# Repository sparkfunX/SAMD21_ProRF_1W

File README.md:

SparkFun SAMD21 Pro RF 1W 
========================================

[*SparkFun SAMD21 Pro RF 1W  (SPX-14984)*](https://www.sparkfun.com/products/14984)

LoRa stands for 'Long-Range,' referring to a modulation technique whose specialty is low power transmission of small data packets -- perfect for Internet of Things applications. Using either point-to-point radio or LoRaWAN you can send data from a node in a remote location back to your base station to check in on sensors or track equipment. Communication is possible in the other direction as well to send commands or control actuators!

Like the [LoRa®-enabled SparkX Pro RF](https://www.sparkfun.com/products/14785) this board is based on the Semtech SX1276 transceiver, but the module boasts a whopping 1W output power. All that extra oomph makes it possible to send small messages up to 9 miles using common rubber-duck type antennas. 

In addition to more transmission power the SparkX SAMD21 ProRF 1W gets more computational power courtesy of the SAMD21 microcontroller running at 48 MHz. We used the additional GPIO pins to permanently enable LoRaWAN signals. This means more pins for you to connect to sensors and actuators, even when connecting to a LoRaWAN network like [The Things Network](https://console.thethingsnetwork.org/). 

SparkFun labored with love to create this code. Feel like supporting open source hardware? 
Buy a [board](https://www.sparkfun.com/products/14984) from SparkFun!

Repository Contents
-------------------

* **/Documents** - Datasheets
* **/Hardware** - Eagle design files (.brd, .sch)

License Information
-------------------

This product is _**open source**_! 

If you have any questions or concerns on licensing, please contact techsupport@sparkfun.com.

Please use, reuse, and modify these files as you see fit. Please maintain attribution to SparkFun Electronics and release any derivative under the same license.

Distributed as-is; no warranty is given.

- Your friends at SparkFun.

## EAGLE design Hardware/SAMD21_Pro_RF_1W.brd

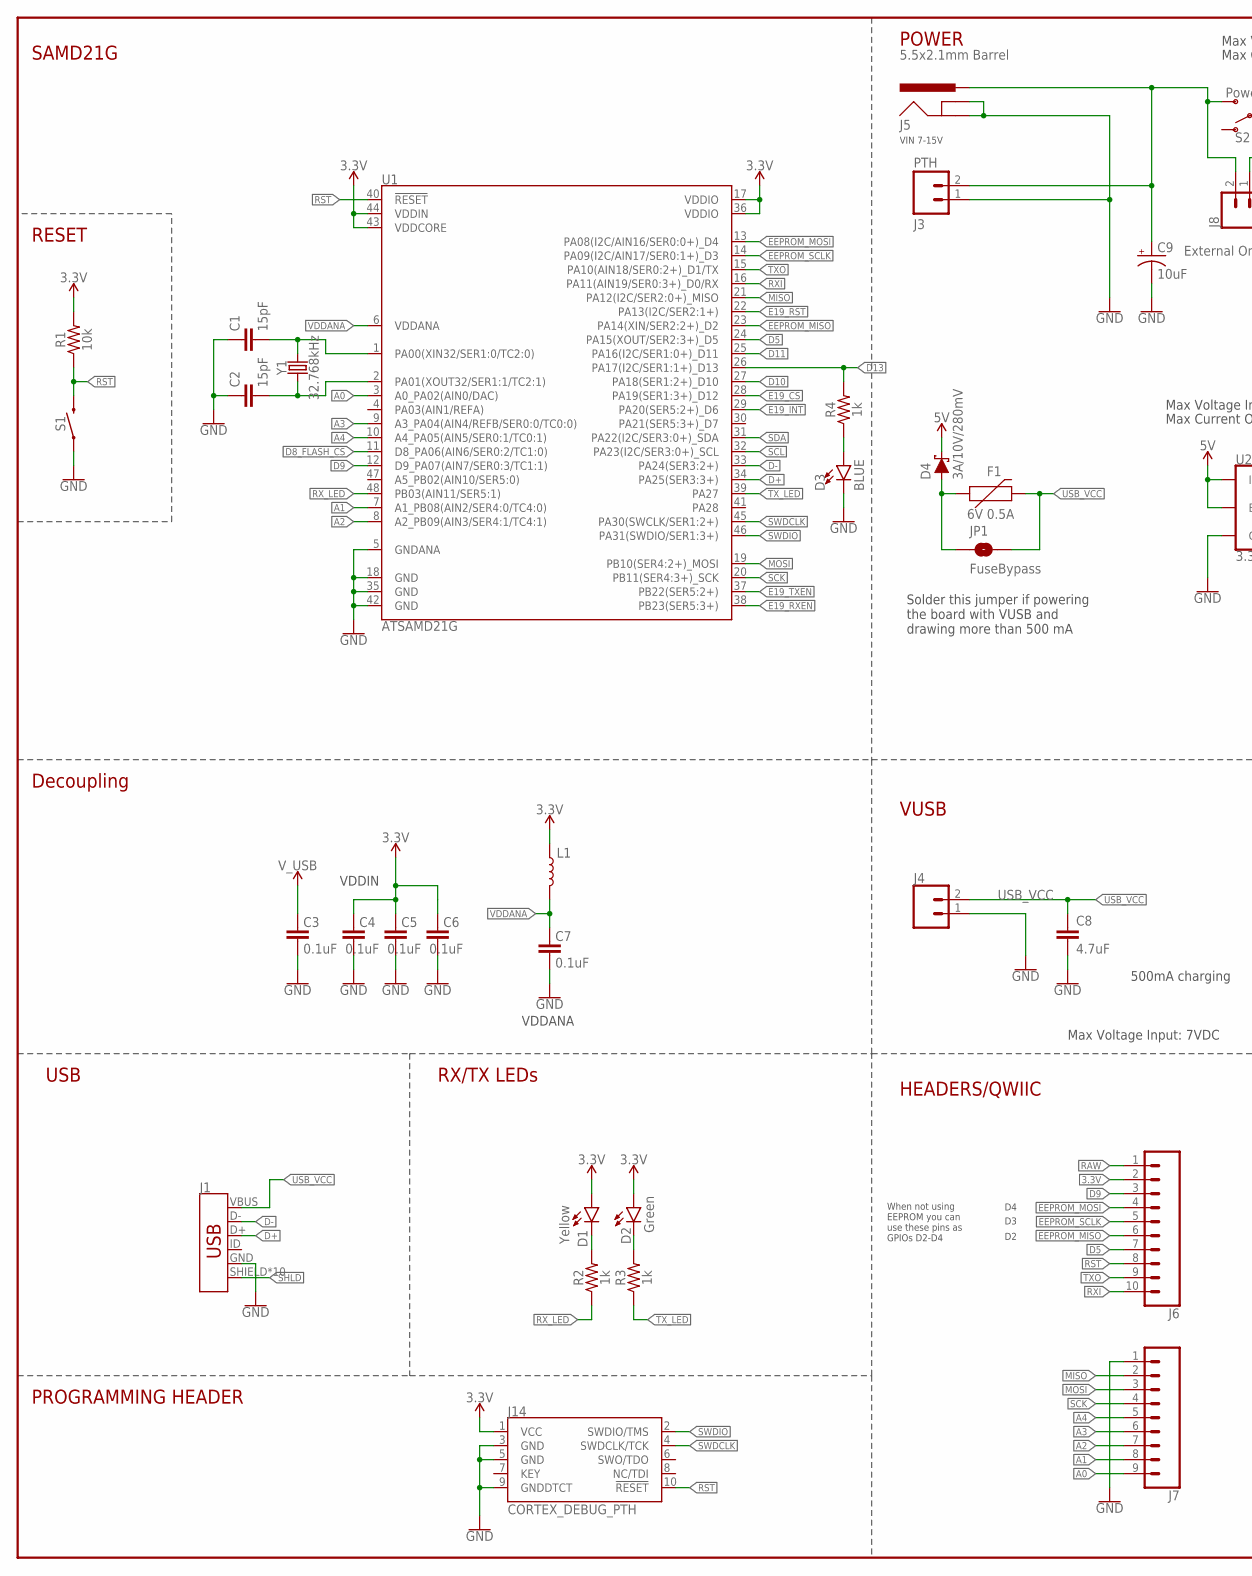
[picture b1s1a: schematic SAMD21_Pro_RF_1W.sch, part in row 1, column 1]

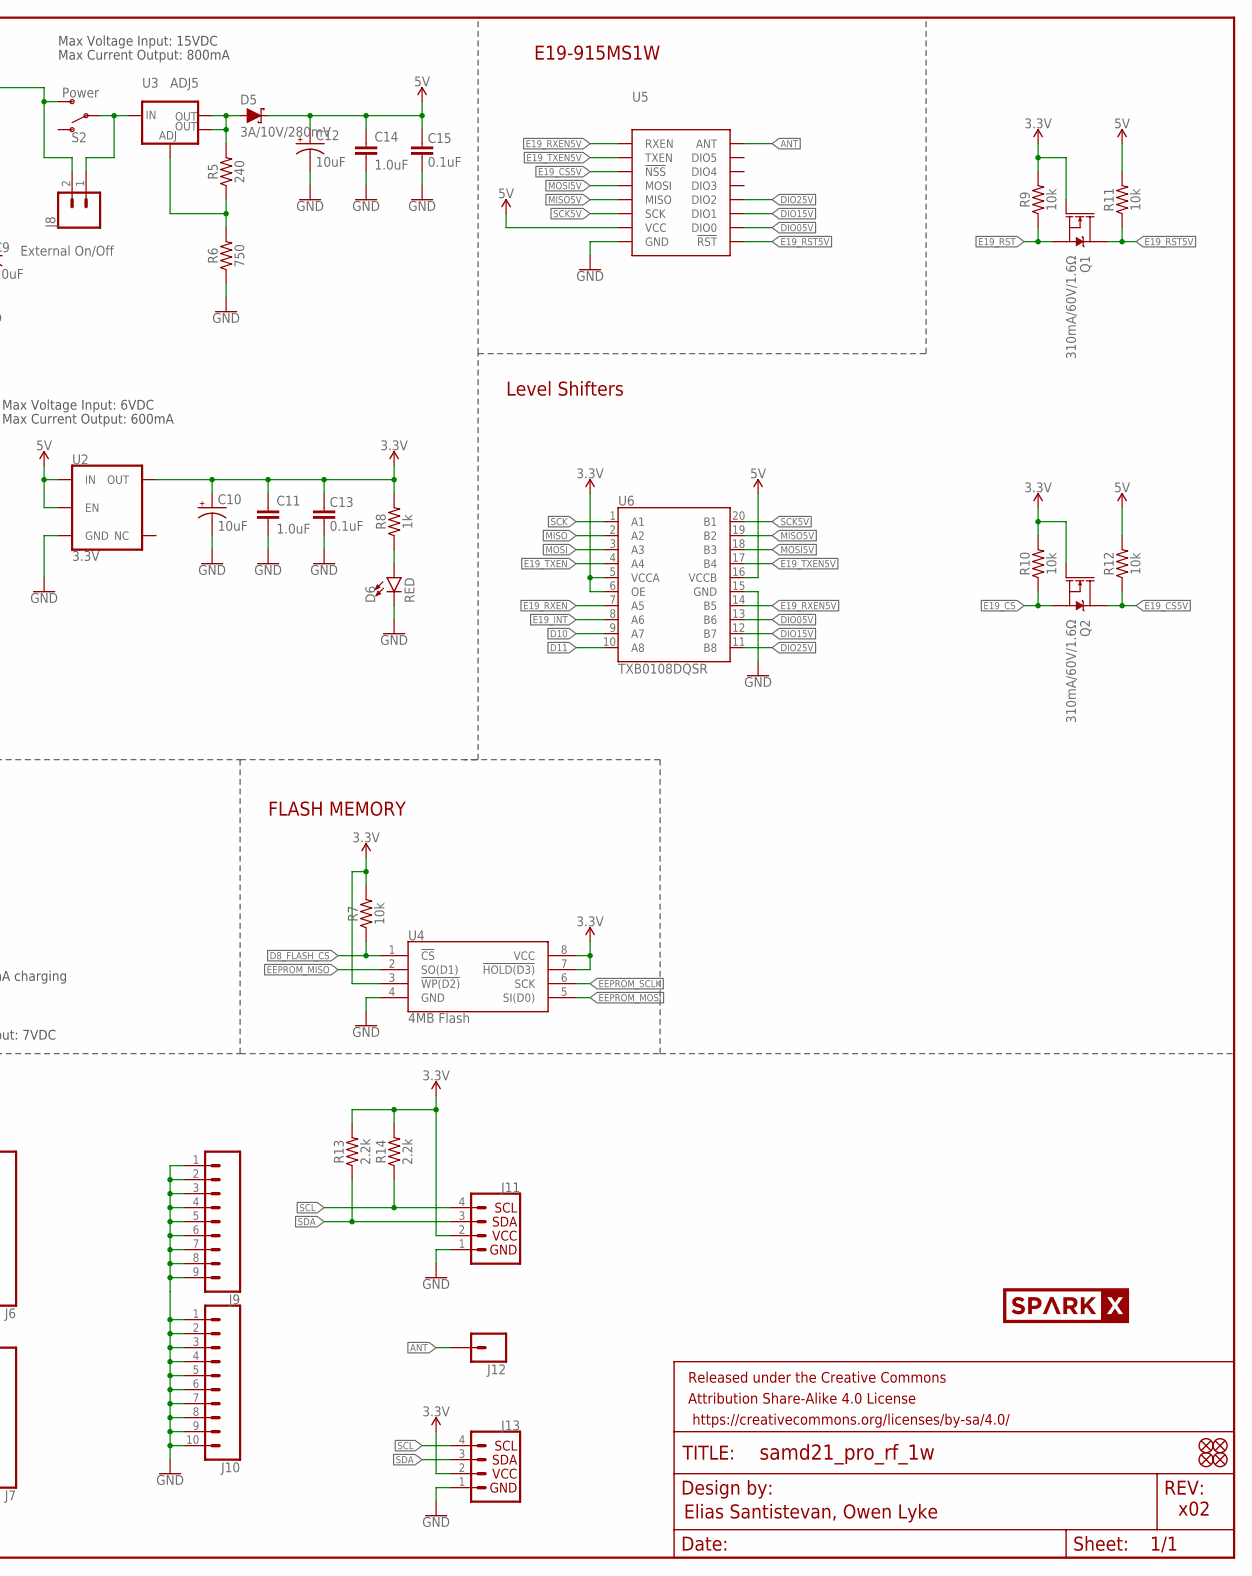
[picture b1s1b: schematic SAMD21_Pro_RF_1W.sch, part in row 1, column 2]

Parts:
C1, C2: 15pF; 0603
C3, C4, C5, C6, C7, C13, C15: 0.1uF; 0603
C8: 4.7uF; 0603
C9, C10, C12: 10uF; EIA3216
C11, C14: 1.0uF; 0603
D1: Yellow; LED-0603
D2: Green; LED-0603
D3: BLUE; LED-0603
D4, D5: 3A/10V/280mV; SOD-323
D6: RED; LED-0603
F1: 6V 0.5A; 0805
FD1, FD2, FD3, FD4: FIDUCIAL1X2; FIDUCIAL-1X2
FRAME1: FRAME-LEDGER; CREATIVE_COMMONS
J1: USB_MICRO-B_HALF_PTH_MILL; USB-MICROB-PTH-MILL
J3: PTH; 1X02_NO_SILK
J4: CONN_021X02_NO_SILK; 1X02_NO_SILK
J5: 5.5x2.1mm Barrel; POWER_JACK_SMD
J6, J10: CONN_10NO_SILK_PTH_FEMALE; 1X10_NO_SILK
J7, J9: CONN_09NO_SILK; 1X09_NO_SILK
J8: External On/Off; 1X02_NO_SILK
J11, J13: QWIIC_CONNECTORJS-1MM; 1X04_1MM_RA
J12: CONN_01PTH_NO_SILK_YES_STOP; 1X01_NO_SILK
J14: CORTEX_DEBUG_PTH; 2X5-PTH-1.27MM
JP1: FuseBypass; SMT-JUMPER_2_NO_SILK
L1: INDUCTORFB-30OHM; 0603
Q1, Q2: 310mA/60V/1.6Ω; SOT323
R1, R7, R9, R10, R11, R12: 10k; 0603
R2, R3, R4, R8: 1k; 0603
R5: 240; 0603
R6: 750; 0603
R13, R14: 2.2k; 0603
S1: MOMENTARY-SWITCH-SPST-SMD-5.2-REDUNDANT; TACTILE_SWITCH_SMD_5.2MM
S2: Power; SWITCH_SPST_SMD_A
U1: ATSAMD21G; QFN-48_NO_EXPOSED_PAD
U2: 3.3V; SOT23-5
U3: ADJ5; SOT223
U4: 4MB Flash; SO08
U5: E19-915MS1W
U6: TXB0108DQSR; UFDFN-20
U$34: SPARKX-LOGO4; SPARKX-MEDIUM
Y1: 32.768kHz; CRYSTAL-SMD-3.2X1.5MM

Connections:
3.3V: C4.2, C5.2, C6.2, C10.+, C11.1, C13.2, D1.A, D2.A, J6.2, J11.2, J13.2, J14.1 (VCC), L1.1, Q1.1 (G), Q2.1 (G), R1.2, R7.2, R8.2, R9.2, R10.2, R13.2, R14.2, U1.17 (VDDIO), U1.36 (VDDIO), U1.43 (VDDCORE), U1.44 (VDDIN), U2.5 (OUT), U4.3 (!WP(D2)), U4.7 (!HOLD(D3)), U4.8 (VCC), U6.5 (VCCA), U6.6 (OE)
5V: C12.+, C14.1, C15.2, D4.C, D5.C, R11.2, R12.2, U2.1 (IN), U2.3 (EN), U5.P$11 (VCC), U6.16 (VCCB)
!E19_CS: Q2.2 (S), R10.1, U1.28 (PA19(SER1:3+)_D12)
!E19_CS5V: Q2.3 (D), R12.1, U5.P$15 (!NSS)
!E19_RST: Q1.2 (S), R9.1, U1.22 (PA13(I2C/SER2:1+))
!E19_RST5V: Q1.3 (D), R11.1, U5.P$8 (!RST)
!RST: J6.8, J14.10 (!RESET), R1.1, S1.3 (2), S1.4 (2), U1.40 (!RESET!)
A0: J7.9, U1.3 (A0_PA02(AIN0/DAC))
A1: J7.8, U1.7 (A1_PB08(AIN2/SER4:0/TC4:0))
A2: J7.7, U1.8 (A2_PB09(AIN3/SER4:1/TC4:1))
A3: J7.6, U1.9 (A3_PA04(AIN4/REFB/SER0:0/TC0:0))
A4: J7.5, U1.10 (A4_PA05(AIN5/SER0:1/TC0:1))
ANT: J12.1, U5.P$19 (ANT)
D5: J6.7, U1.24 (PA15(XOUT/SER2:3+)_D5)
D8_!FLASH_CS: R7.1, U1.11 (D8_PA06(AIN6/SER0:2/TC1:0)), U4.1 (!CS)
D9: J6.3, U1.12 (D9_PA07(AIN7/SER0:3/TC1:1))
D10: U1.27 (PA18(SER1:2+)_D10), U6.9 (A7)
D11: U1.25 (PA16(I2C/SER1:0+)_D11), U6.10 (A8)
D13: R4.2, U1.26 (PA17(I2C/SER1:1+)_D13)
D+: J1.D+, U1.34 (PA25(SER3:3+))
D-: J1.D-, U1.33 (PA24(SER3:2+))
DIO05V: U5.P$7 (DIO0), U6.13 (B6)
DIO15V: U5.P$6 (DIO1), U6.12 (B7)
DIO25V: U5.P$5 (DIO2), U6.11 (B8)
E19_INT: U1.29 (PA20(SER5:2+)_D6), U6.8 (A6)
E19_RXEN: U1.38 (PB23(SER5:3+)), U6.7 (A5)
E19_RXEN5V: U5.P$17 (RXEN), U6.14 (B5)
E19_TXEN: U1.37 (PB22(SER5:2+)), U6.4 (A4)
E19_TXEN5V: U5.P$16 (TXEN), U6.17 (B4)
EEPROM_MISO: J6.6, U1.23 (PA14(XIN/SER2:2+)_D2), U4.2 (SO(D1))
EEPROM_MOSI: J6.4, U1.13 (PA08(I2C/AIN16/SER0:0+)_D4), U4.5 (SI(D0))
EEPROM_SCLK: J6.5, U1.14 (PA09(I2C/AIN17/SER0:1+)_D3), U4.6 (SCK)
GND: C1.1, C2.1, C3.1, C4.1, C5.1, C6.1, C7.1, C8.2, C9.-, C10.-, C11.2, C12.-, C13.1, C14.2, C15.1, D3.C, D6.C, J1.GND, J3.1, J4.1, J5.GND (GNDBREAK), J5.P$4 (GND), J7.1, J9.1, J9.2, J9.3, J9.4, J9.5, J9.6, J9.7, J9.8, J9.9, J10.1, J10.2, J10.3, J10.4, J10.5, J10.6, J10.7, J10.8, J10.9, J10.10, J11.1, J13.1, J14.3 (GND), J14.5 (GND), J14.9 (GNDDTCT), R6.1, S1.1, S1.2 (1), U1.5 (GNDANA), U1.18 (GND), U1.35 (GND), U1.42 (GND), U2.2 (GND), U4.4 (GND), U5.P$1 (GND), U5.P$9 (GND), U5.P$10 (GND), U5.P$18 (GND), U5.P$20 (GND), U5.P$21 (GND), U5.P$22 (GND), U6.15 (GND)
MISO: J7.2, U1.21 (PA12(I2C/SER2:0+)_MISO), U6.2 (A2)
MISO5V: U5.P$13 (MISO), U6.19 (B2)
MOSI: J7.3, U1.19 (PB10(SER4:2+)_MOSI), U6.3 (A3)
MOSI5V: U5.P$14 (MOSI), U6.18 (B3)
unnamed: D1.C, R2.2
unnamed: D2.C, R3.2
unnamed: D3.A, R4.1
unnamed: C1.2, U1.1 (PA00(XIN32/SER1:0/TC2:0)), Y1.P$2 (2)
unnamed: C2.2, U1.2 (PA01(XOUT32/SER1:1/TC2:1)), Y1.P$1 (1)
unnamed: D4.A, F1.1, JP1.1
unnamed: R5.1, R6.2, U3.1 (ADJ)
unnamed: D5.A, R5.2, U3.2 (OUT), U3.4 (OUT)
unnamed: D6.A, R8.1
RAW: J6.1, J8.1, S2.2, U3.3 (IN)
RXI: J6.10, U1.16 (PA11(AIN19/SER0:3+)_D0/RX)
RX_LED: R2.1, U1.48 (PB03(AIN11/SER5:1))
SCK: J7.4, U1.20 (PB11(SER4:3+)_SCK), U6.1 (A1)
SCK5V: U5.P$12 (SCK), U6.20 (B1)
SCL: J11.4, J13.4, R14.1, U1.32 (PA23(I2C/SER3:0+)_SCL)
SDA: J11.3, J13.3, R13.1, U1.31 (PA22(I2C/SER3:0+)_SDA)
SHLD: J1.SHIELD, J1.SHIELD2 (SHIELD), J1.SHIELD3 (SHIELD), J1.SHIELD4 (SHIELD), J1.SHIELD5 (SHIELD), J1.SHIELD6 (SHIELD), J1.SHIELD7 (SHIELD), J1.SHIELD8 (SHIELD), J1.SHIELD9 (SHIELD), J1.SHIELD10 (SHIELD)
SWDCLK: J14.4 (SWDCLK/TCK), U1.45 (PA30(SWCLK/SER1:2+))
SWDIO: J14.2 (SWDIO/TMS), U1.46 (PA31(SWDIO/SER1:3+))
TXO: J6.9, U1.15 (PA10(AIN18/SER0:2+)_D1/TX)
TX_LED: R3.1, U1.39 (PA27)
VBATT: C9.+, J3.2, J5.VIN0 (PWR), J8.2, S2.3 (S)
VDDANA: C7.2, L1.2, U1.6 (VDDANA)

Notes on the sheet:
Solder this jumper if powering the board with VUSB and drawing more than 500 mA
500mA charging
VDDIN
VDDANA
Decoupling
SAMD21G
Elias Santistevan, Owen Lyke
x02
POWER
VUSB
FLASH MEMORY
E19-915MS1W
RESET
HEADERS/QWIIC
USB
PROGRAMMING HEADER
RX/TX LEDs
Max Voltage Input: 15VDC
Max Current Output: 800mA
Level Shifters
VIN 7-15V
Max Voltage Input: 7VDC
Max Voltage Input: 6VDC
Max Current Output: 600mA
When not using EEPROM you can use these pins as GPIOs D2-D4

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
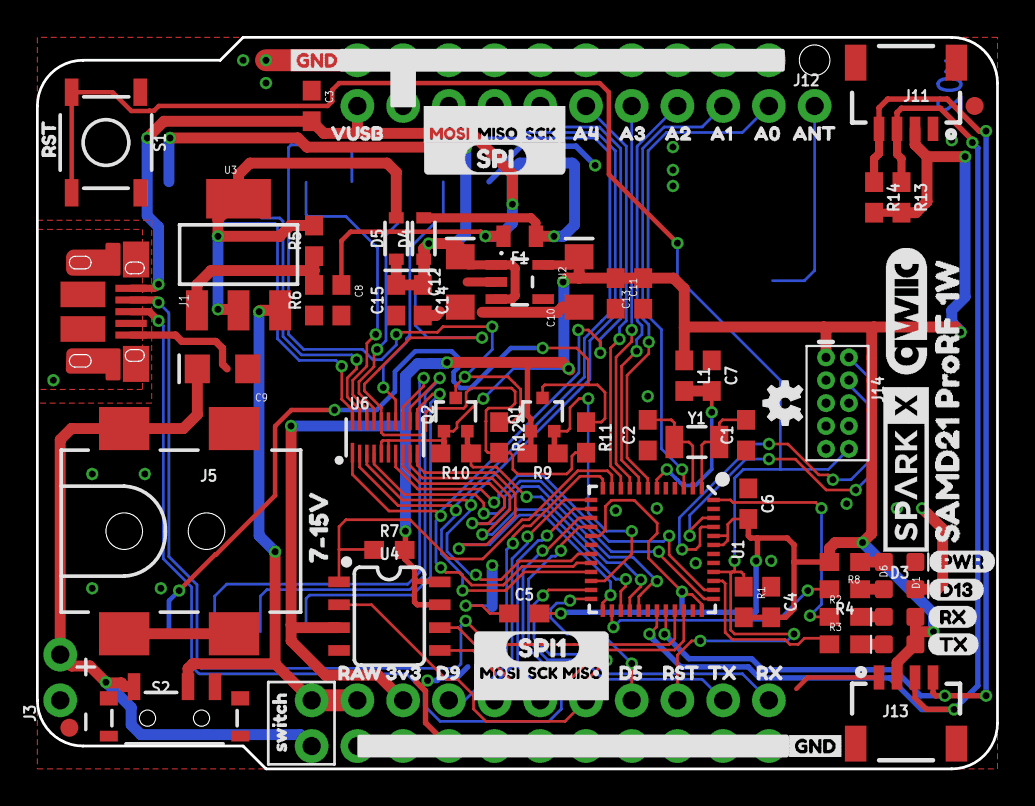
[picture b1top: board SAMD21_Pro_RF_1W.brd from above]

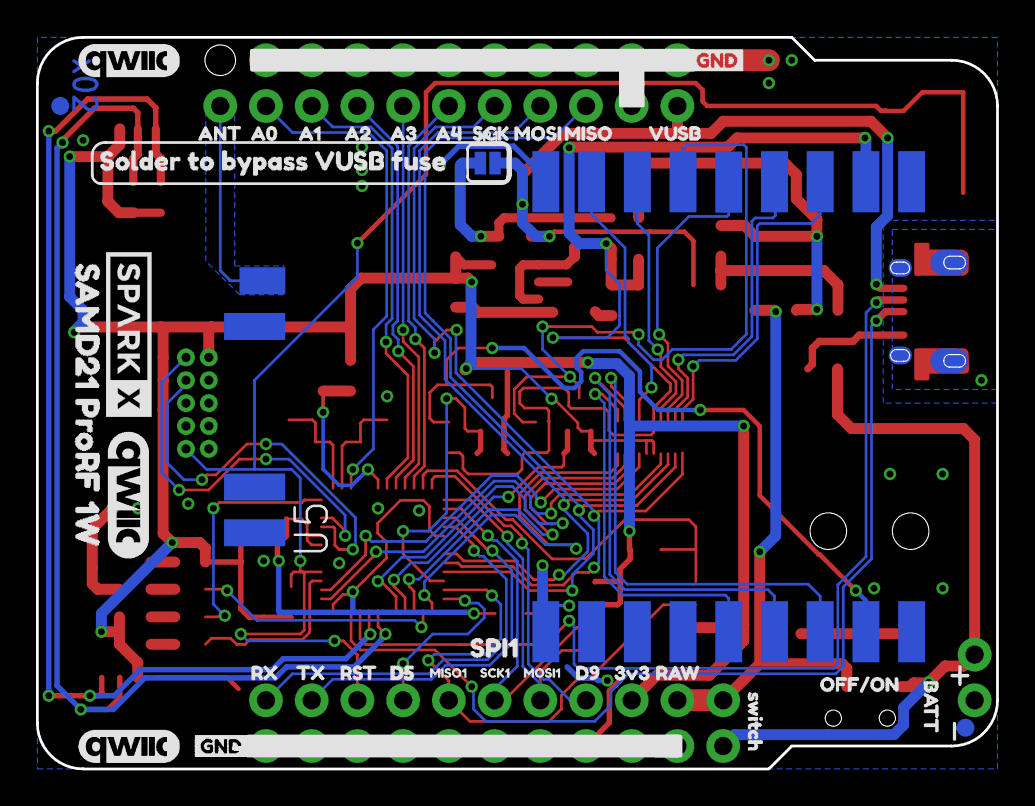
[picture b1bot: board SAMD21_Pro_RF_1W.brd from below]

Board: 2 copper layers, 53.3 x 40.6 mm, 134 parts (36 on the bottom side), 61 nets.

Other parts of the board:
U$1, U$14: VUSB7
U$2, U$10: MISO4
U$3, U$42: A43
U$4, U$43: A34
U$5, U$44: A25
U$6, U$45: A16
U$7, U$46: A07
U$8: SPI2
U$9, U$20: MOSI3
U$11, U$50: ANT11
U$12, U$17, U$38, U$62: GND0
U$13, U$28, U$41: RST2
U$15, U$16: D90
U$18, U$39: SCK5
U$19, U$73: RX2
U$21, U$65: SPI11
U$22: MISO17
U$23, U$53: 3V320
U$24, U$52: RAW21
U$25: 7#15V0
U$26, U$81: SAMD21_PRORF_1W5
U$27, U$37: SWITCH6
U$30, U$51: QWIIC_COPYRIGHT_MEDIUM
U$31: MOSI16
U$32: BATT25
U$33: D50
U$35: SOLDER_TO_BYPASS_VUSB_FUSE1
U$36: OFF#ON1
U$47: MISO8
U$48: MOSI9
U$49: SCK10
U$55: D514
U$57, U$69: TX3
U$58: SPARKX-MEDIUM
U$59: D130
U$60: SCK18
U$61: OSHW-LOGO-MINI
U$63: PWR-()-03
U$64, U$67: QWIIC_COPYRIGHT_SMALL
U$70: TX6
U$72: RX7

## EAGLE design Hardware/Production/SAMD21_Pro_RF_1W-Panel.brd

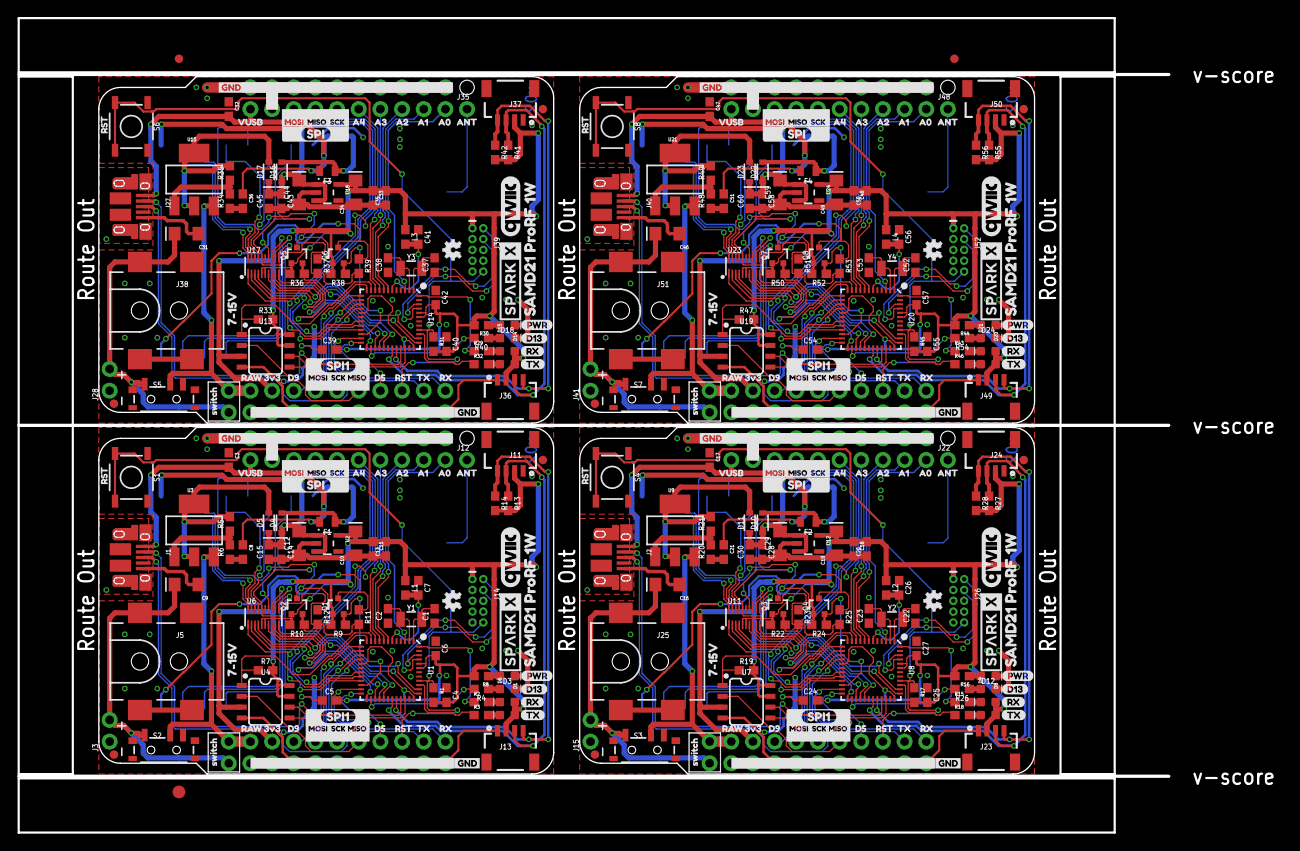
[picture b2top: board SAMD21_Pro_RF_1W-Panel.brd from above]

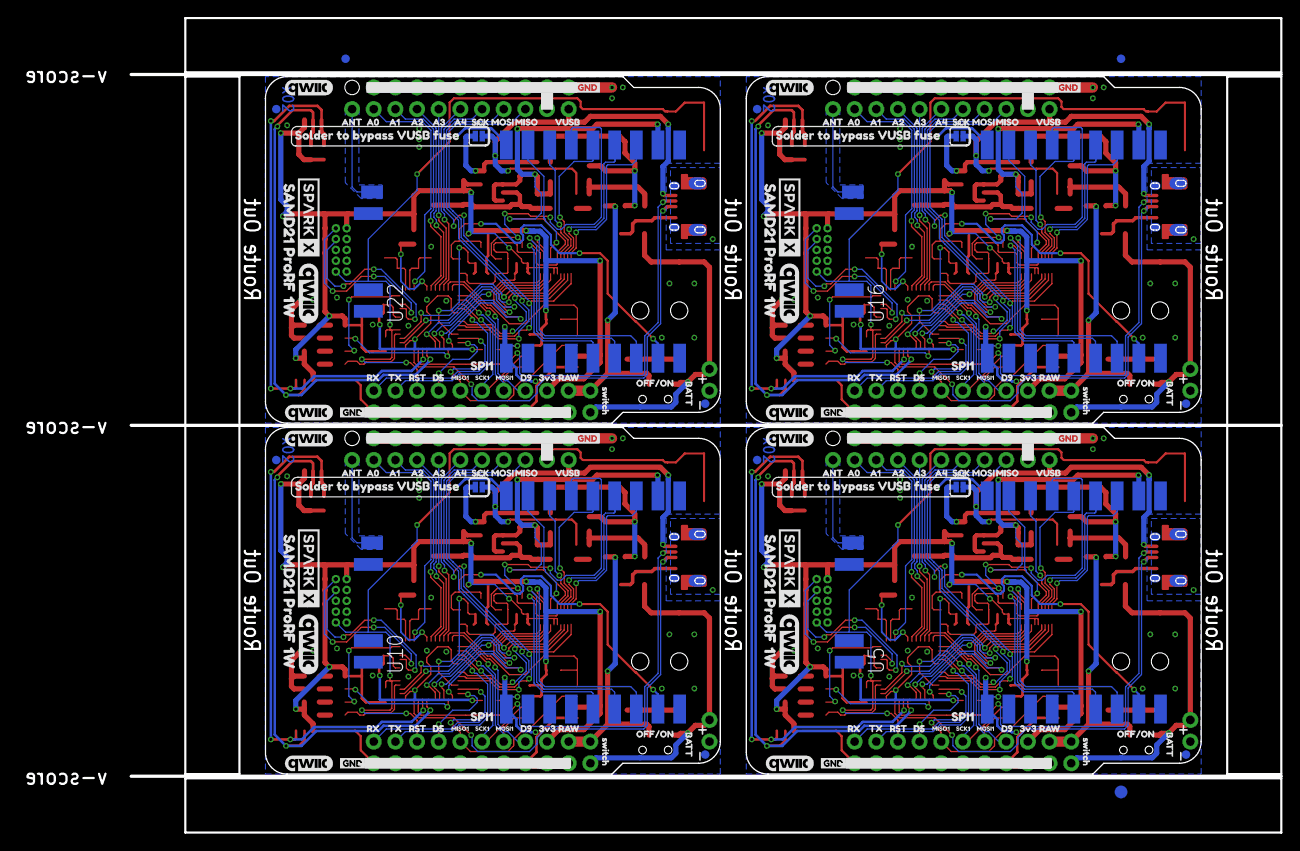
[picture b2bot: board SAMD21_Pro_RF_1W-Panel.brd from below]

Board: 2 copper layers, 148.1 x 95.4 mm, 538 parts (147 on the bottom side), 244 nets.

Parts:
C1, C2, C22, C23, C37, C38, C52, C53: 15pF; 0603
C3, C4, C5, C6, C7, C13, C15, C17, C20, C24, C25, C26, C27, C30, C32, C35, C39, C40, C41, C42, C45, C47, C50, C54, C55, C56, C57, C60: 0.1uF; 0603
C8, C21, C36, C51: 4.7uF; 0603
C9, C10, C12, C16, C19, C29, C31, C34, C44, C46, C49, C59: 10uF; EIA3216
C11, C14, C18, C28, C33, C43, C48, C58: 1.0uF; 0603
D1, D8, D14, D20: Yellow; LED-0603
D2, D7, D13, D19: Green; LED-0603
D3, D12, D18, D24: BLUE; LED-0603
D4, D5, D10, D11, D16, D17, D22, D23: 3A/10V/300mV; SOD-323
D6, D9, D15, D21: RED; LED-0603
E$1, E$2, E$3, E$4: FIDUCIAL-1X2
E$5, E$6: FIDUCIAL-1.5X3
F1, F2, F3, F4: 6V 0.5A; 0805
FD1, FD2, FD3, FD4, FD5, FD6, FD7, FD8, FD9, FD10, FD11, FD12, FD13, FD14, FD15, FD16: FIDUCIAL1X2; FIDUCIAL-1X2
J1, J2, J27, J40: USB-MICROB-PTH-MILL
J3, J15, J28, J41: PTH; 1X02_NO_SILK
J4, J16, J29, J42: 1X02_NO_SILK
J5, J25, J38, J51: 5.5x2.1mm Barrel; POWER_JACK_SMD
J6, J10, J18, J19, J31, J32, J44, J45: 1X10_NO_SILK
J7, J9, J20, J21, J33, J34, J46, J47: 1X09_NO_SILK
J8, J17, J30, J43: External On/Off; 1X02_NO_SILK
J11, J13, J23, J24, J36, J37, J49, J50: 1X04_1MM_RA
J12, J22, J35, J48: 1X01_NO_SILK
J14, J26, J39, J52: CORTEX_DEBUG_PTH; 2X5-PTH-1.27MM
JP1, JP2, JP3, JP4: FuseBypass; SMT-JUMPER_2_NO_SILK
L1, L2, L3, L4: 0603
Q1, Q2, Q3, Q4, Q5, Q6, Q7, Q8: 310mA/60V/1.6Ω; SOT323
R1, R7, R9, R10, R11, R12, R17, R19, R22, R23, R24, R25, R31, R33, R36, R37, R38, R39, R45, R47, R50, R51, R52, R53: 10k; 0603
R2, R3, R4, R8, R15, R16, R18, R26, R29, R30, R32, R40, R43, R44, R46, R54: 1k; 0603
R5, R21, R35, R49: 240; 0603
R6, R20, R34, R48: 750; 0603
R13, R14, R27, R28, R41, R42, R55, R56: 2.2k; 0603
S1, S4, S6, S8: MOMENTARY-SWITCH-SPST-SMD-5.2-REDUNDANT; TACTILE_SWITCH_SMD_5.2MM
S2, S3, S5, S7: Power; SWITCH_SPST_SMD_A
U1, U8, U14, U20: ATSAMD21G; QFN-48_NO_EXPOSED_PAD
U2, U12, U18, U24: 3.3V; SOT23-5
U3, U9, U15, U21: ADJ5; SOT223
U4, U7, U13, U19: 4MB Flash; SO08
U5, U10, U16, U22: E19-915MS1W
U6, U11, U17, U23: TXB0108DQSR; UFDFN-20
U$1, U$14, U$108, U$109, U$175, U$176, U$242, U$243: VUSB7
U$2, U$10, U$121, U$123, U$188, U$190, U$255, U$257: MISO4
U$3, U$29, U$42, U$82, U$135, U$149, U$202, U$216: A43
U$4, U$40, U$43, U$83, U$136, U$150, U$203, U$217: A34
U$5, U$44, U$54, U$84, U$137, U$151, U$204, U$218: A25
U$6, U$45, U$56, U$85, U$138, U$152, U$205, U$219: A16
U$7, U$46, U$66, U$86, U$139, U$153, U$206, U$220: A07
U$8, U$119, U$186, U$253: SPI2
U$9, U$20, U$120, U$125, U$187, U$192, U$254, U$259: MOSI3
U$11, U$50, U$68, U$90, U$140, U$157, U$207, U$224: ANT11
U$12, U$17, U$38, U$62, U$71, U$79, U$93, U$102, U$141, U$147, U$160, U$169, U$208, U$214, U$227, U$236: GND0
U$13, U$28, U$41, U$74, U$77, U$80, U$142, U$145, U$148, U$209, U$212, U$215: RST2
U$15, U$16, U$100, U$101, U$167, U$168, U$234, U$235: D90
U$18, U$39, U$122, U$124, U$189, U$191, U$256, U$258: SCK5
U$19, U$73, U$98, U$103, U$165, U$170, U$232, U$237: RX2
U$21, U$65, U$126, U$127, U$193, U$194, U$260, U$261: SPI11
U$22, U$128, U$195, U$262: MISO17
U$23, U$53, U$75, U$92, U$143, U$159, U$210, U$226: 3V320
U$24, U$52, U$76, U$91, U$144, U$158, U$211, U$225: RAW21
U$25, U$112, U$179, U$246: 7#15V0
U$26, U$81, U$107, U$115, U$174, U$182, U$241, U$249: SAMD21_PRORF_1W5
U$27, U$37, U$110, U$111, U$177, U$178, U$244, U$245: SWITCH6
U$30, U$51, U$133, U$134, U$200, U$201, U$267, U$268: QWIIC_COPYRIGHT_MEDIUM
U$31, U$129, U$196, U$263: MOSI16
U$32, U$78, U$146, U$213: BATT25
U$33, U$105, U$172, U$239: D50
U$34, U$114, U$181, U$248: SPARKX-LOGO4; SPARKX-MEDIUM
U$35, U$113, U$180, U$247: SOLDER_TO_BYPASS_VUSB_FUSE1
U$36, U$118, U$185, U$252: OFF#ON1
U$47, U$87, U$154, U$221: MISO8
U$48, U$88, U$155, U$222: MOSI9
U$49, U$89, U$156, U$223: SCK10
U$55, U$99, U$166, U$233: D514
U$57, U$69, U$95, U$104, U$162, U$171, U$229, U$238: TX3
U$58, U$116, U$183, U$250: SPARKX-MEDIUM
U$59, U$117, U$184, U$251: D130
U$60, U$130, U$197, U$264: SCK18
U$61, U$106, U$173, U$240: OSHW-LOGO-MINI
U$63, U$94, U$161, U$228: PWR-()-03
U$64, U$67, U$131, U$132, U$198, U$199, U$265, U$266: QWIIC_COPYRIGHT_SMALL
U$70, U$96, U$163, U$230: TX6
U$72, U$97, U$164, U$231: RX7
Y1, Y2, Y3, Y4: 32.768kHz; CRYSTAL-SMD-3.2X1.5MM

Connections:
3.3V: C4.2, C5.2, C6.2, C10.+, C11.1, C13.2, D1.A, D2.A, J6.2, J11.2, J13.2, J14.1, L1.1, Q1.1, Q2.1, R1.2, R7.2, R8.2, R9.2, R10.2, R13.2, R14.2, U1.17, U1.36, U1.43, U1.44, U2.5, U4.3, U4.7, U4.8, U6.5, U6.6
3.3V1: C18.1, C19.+, C20.2, C24.2, C25.2, C27.2, D7.A, D8.A, J18.2, J23.2, J24.2, J26.1, L2.1, Q3.1, Q4.1, R16.2, R17.2, R19.2, R22.2, R24.2, R27.2, R28.2, U7.3, U7.7, U7.8, U8.17, U8.36, U8.43, U8.44, U11.5, U11.6, U12.5
3.3V2: C33.1, C34.+, C35.2, C39.2, C40.2, C42.2, D13.A, D14.A, J31.2, J36.2, J37.2, J39.1, L3.1, Q5.1, Q6.1, R30.2, R31.2, R33.2, R36.2, R38.2, R41.2, R42.2, U13.3, U13.7, U13.8, U14.17, U14.36, U14.43, U14.44, U17.5, U17.6, U18.5
3.3V3: C48.1, C49.+, C50.2, C54.2, C55.2, C57.2, D19.A, D20.A, J44.2, J49.2, J50.2, J52.1, L4.1, Q7.1, Q8.1, R44.2, R45.2, R47.2, R50.2, R52.2, R55.2, R56.2, U19.3, U19.7, U19.8, U20.17, U20.36, U20.43, U20.44, U23.5, U23.6, U24.5
5V: C12.+, C14.1, C15.2, D4.C, D5.C, R11.2, R12.2, U2.1, U2.3, U5.P$11, U6.16
5V1: C28.1, C29.+, C30.2, D10.C, D11.C, R23.2, R25.2, U10.P$11, U11.16, U12.1, U12.3
5V2: C43.1, C44.+, C45.2, D16.C, D17.C, R37.2, R39.2, U16.P$11, U17.16, U18.1, U18.3
5V3: C58.1, C59.+, C60.2, D22.C, D23.C, R51.2, R53.2, U22.P$11, U23.16, U24.1, U24.3
!E19_CS: Q2.2, R10.1, U1.28
!E19_CS1: Q3.2, R22.1, U8.28
!E19_CS2: Q5.2, R36.1, U14.28
!E19_CS3: Q7.2, R50.1, U20.28
!E19_CS5V: Q2.3, R12.1, U5.P$15
!E19_CS5V1: Q3.3, R23.1, U10.P$15
!E19_CS5V2: Q5.3, R37.1, U16.P$15
!E19_CS5V3: Q7.3, R51.1, U22.P$15
!E19_RST: Q1.2, R9.1, U1.22
!E19_RST1: Q4.2, R24.1, U8.22
!E19_RST2: Q6.2, R38.1, U14.22
!E19_RST3: Q8.2, R52.1, U20.22
!E19_RST5V: Q1.3, R11.1, U5.P$8
!E19_RST5V1: Q4.3, R25.1, U10.P$8
!E19_RST5V2: Q6.3, R39.1, U16.P$8
!E19_RST5V3: Q8.3, R53.1, U22.P$8
!RST: J6.8, J14.10, R1.1, S1.3, S1.4, U1.40
!RST1: J18.8, J26.10, R17.1, S4.3, S4.4, U8.40
!RST2: J31.8, J39.10, R31.1, S6.3, S6.4, U14.40
!RST3: J44.8, J52.10, R45.1, S8.3, S8.4, U20.40
A0: J7.9, U1.3
A1: J7.8, U1.7
A2: J7.7, U1.8
A3: J7.6, U1.9
A4: J7.5, U1.10
A5: J21.9, U8.3
A6: J21.8, U8.7
A7: J21.7, U8.8
A8: J21.6, U8.9
A9: J21.5, U8.10
A10: J34.9, U14.3
A11: J34.8, U14.7
A12: J34.7, U14.8
A13: J34.6, U14.9
A14: J34.5, U14.10
A15: J47.9, U20.3
A16: J47.8, U20.7
A17: J47.7, U20.8
A18: J47.6, U20.9
A19: J47.5, U20.10
ANT: J12.1, U5.P$19
ANT1: J22.1, U10.P$19
ANT2: J35.1, U16.P$19
ANT3: J48.1, U22.P$19
D1: U8.27, U11.9
D2: U8.25, U11.10
D3: J18.7, U8.24
D4: J18.3, U8.12
D5: J6.7, U1.24
D6: R26.2, U8.26
D7: U14.27, U17.9
D8: U14.25, U17.10
D8_!FLASH_CS: R7.1, U1.11, U4.1
D8_!FLASH_CS1: R19.1, U7.1, U8.11
D8_!FLASH_CS2: R33.1, U13.1, U14.11
D8_!FLASH_CS3: R47.1, U19.1, U20.11
D9: J6.3, U1.12
D10: U1.27, U6.9
D11: U1.25, U6.10
D12: J31.7, U14.24
D13: R4.2, U1.26
D14: J31.3, U14.12
D15: R40.2, U14.26
D16: U20.27, U23.9
D17: U20.25, U23.10
D18: J44.7, U20.24
D19: J44.3, U20.12
D20: R54.2, U20.26
D+: J1.D+, U1.34
D+1: J2.D+, U8.34
D+2: J27.D+, U14.34
D+3: J40.D+, U20.34
D-: J1.D-, U1.33
D-1: J2.D-, U8.33
D-2: J27.D-, U14.33
D-3: J40.D-, U20.33
DIO05V: U5.P$7, U6.13
DIO05V1: U10.P$7, U11.13
DIO05V2: U16.P$7, U17.13
DIO05V3: U22.P$7, U23.13
DIO15V: U5.P$6, U6.12
DIO15V1: U10.P$6, U11.12
DIO15V2: U16.P$6, U17.12
DIO15V3: U22.P$6, U23.12
DIO25V: U5.P$5, U6.11
DIO25V1: U10.P$5, U11.11
DIO25V2: U16.P$5, U17.11
DIO25V3: U22.P$5, U23.11
E19_INT: U1.29, U6.8
E19_INT1: U8.29, U11.8
E19_INT2: U14.29, U17.8
E19_INT3: U20.29, U23.8
E19_RXEN: U1.38, U6.7
E19_RXEN1: U8.38, U11.7
E19_RXEN2: U14.38, U17.7
E19_RXEN3: U20.38, U23.7
E19_RXEN5V: U5.P$17, U6.14
E19_RXEN5V1: U10.P$17, U11.14
E19_RXEN5V2: U16.P$17, U17.14
E19_RXEN5V3: U22.P$17, U23.14
E19_TXEN: U1.37, U6.4
E19_TXEN1: U8.37, U11.4
E19_TXEN2: U14.37, U17.4
E19_TXEN3: U20.37, U23.4
E19_TXEN5V: U5.P$16, U6.17
E19_TXEN5V1: U10.P$16, U11.17
E19_TXEN5V2: U16.P$16, U17.17
E19_TXEN5V3: U22.P$16, U23.17
EEPROM_MISO: J6.6, U1.23, U4.2
EEPROM_MISO1: J18.6, U7.2, U8.23
EEPROM_MISO2: J31.6, U13.2, U14.23
EEPROM_MISO3: J44.6, U19.2, U20.23
EEPROM_MOSI: J6.4, U1.13, U4.5
EEPROM_MOSI1: J18.4, U7.5, U8.13
EEPROM_MOSI2: J31.4, U13.5, U14.13
EEPROM_MOSI3: J44.4, U19.5, U20.13
EEPROM_SCLK: J6.5, U1.14, U4.6
EEPROM_SCLK1: J18.5, U7.6, U8.14
EEPROM_SCLK2: J31.5, U13.6, U14.14
EEPROM_SCLK3: J44.5, U19.6, U20.14
GND: C1.1, C2.1, C3.1, C4.1, C5.1, C6.1, C7.1, C8.2, C9.-, C10.-, C11.2, C12.-, C13.1, C14.2, C15.1, D3.C, D6.C, J1.GND, J3.1, J4.1, J5.GND, J5.P$4, J7.1, J9.1, J9.2, J9.3, J9.4, J9.5, J9.6, J9.7, J9.8, J9.9, J10.1, J10.2, J10.3, J10.4, J10.5, J10.6, J10.7, J10.8, J10.9, J10.10, J11.1, J13.1, J14.3, J14.5, J14.9, R6.1, S1.1, S1.2, U1.5, U1.18, U1.35, U1.42, U2.2, U4.4, U5.P$1, U5.P$9, U5.P$10, U5.P$18, U5.P$20, U5.P$21, U5.P$22, U6.15
GND1: C16.-, C17.1, C18.2, C19.-, C20.1, C21.2, C22.1, C23.1, C24.1, C25.1, C26.1, C27.1, C28.2, C29.-, C30.1, D9.C, D12.C, J2.GND, J15.1, J16.1, J19.1, J19.2, J19.3, J19.4, J19.5, J19.6, J19.7, J19.8, J19.9, J19.10, J20.1, J20.2, J20.3, J20.4, J20.5, J20.6, J20.7, J20.8, J20.9, J21.1, J23.1, J24.1, J25.GND, J25.P$4, J26.3, J26.5, J26.9, R20.1, S4.1, S4.2, U7.4, U8.5, U8.18, U8.35, U8.42, U10.P$1, U10.P$9, U10.P$10, U10.P$18, U10.P$20, U10.P$21, U10.P$22, U11.15, U12.2
GND2: C31.-, C32.1, C33.2, C34.-, C35.1, C36.2, C37.1, C38.1, C39.1, C40.1, C41.1, C42.1, C43.2, C44.-, C45.1, D15.C, D18.C, J27.GND, J28.1, J29.1, J32.1, J32.2, J32.3, J32.4, J32.5, J32.6, J32.7, J32.8, J32.9, J32.10, J33.1, J33.2, J33.3, J33.4, J33.5, J33.6, J33.7, J33.8, J33.9, J34.1, J36.1, J37.1, J38.GND, J38.P$4, J39.3, J39.5, J39.9, R34.1, S6.1, S6.2, U13.4, U14.5, U14.18, U14.35, U14.42, U16.P$1, U16.P$9, U16.P$10, U16.P$18, U16.P$20, U16.P$21, U16.P$22, U17.15, U18.2
GND3: C46.-, C47.1, C48.2, C49.-, C50.1, C51.2, C52.1, C53.1, C54.1, C55.1, C56.1, C57.1, C58.2, C59.-, C60.1, D21.C, D24.C, J40.GND, J41.1, J42.1, J45.1, J45.2, J45.3, J45.4, J45.5, J45.6, J45.7, J45.8, J45.9, J45.10, J46.1, J46.2, J46.3, J46.4, J46.5, J46.6, J46.7, J46.8, J46.9, J47.1, J49.1, J50.1, J51.GND, J51.P$4, J52.3, J52.5, J52.9, R48.1, S8.1, S8.2, U19.4, U20.5, U20.18, U20.35, U20.42, U22.P$1, U22.P$9, U22.P$10, U22.P$18, U22.P$20, U22.P$21, U22.P$22, U23.15, U24.2
MISO: J7.2, U1.21, U6.2
MISO1: J21.2, U8.21, U11.2
MISO2: J34.2, U14.21, U17.2
MISO3: J47.2, U20.21, U23.2
MISO5V: U5.P$13, U6.19
MISO5V1: U10.P$13, U11.19
MISO5V2: U16.P$13, U17.19
MISO5V3: U22.P$13, U23.19
MOSI: J7.3, U1.19, U6.3
MOSI1: J21.3, U8.19, U11.3
MOSI2: J34.3, U14.19, U17.3
MOSI3: J47.3, U20.19, U23.3
MOSI5V: U5.P$14, U6.18
MOSI5V1: U10.P$14, U11.18
MOSI5V2: U16.P$14, U17.18
MOSI5V3: U22.P$14, U23.18
unnamed: D1.C, R2.2
unnamed: D2.C, R3.2
unnamed: D3.A, R4.1
unnamed: D9.A, R16.1
unnamed: D8.C, R15.2
unnamed: C1.2, U1.1, Y1.P$2
unnamed: C2.2, U1.2, Y1.P$1
unnamed: D7.C, R18.2
unnamed: C22.2, U8.1, Y2.P$2
unnamed: C23.2, U8.2, Y2.P$1
unnamed: R20.2, R21.1, U9.1
unnamed: D4.A, F1.1, JP1.1
unnamed: R5.1, R6.2, U3.1
unnamed: D5.A, R5.2, U3.2, U3.4
unnamed: D10.A, F2.1, JP2.1
unnamed: D11.A, R21.2, U9.2, U9.4
unnamed: D12.A, R26.1
unnamed: D15.A, R30.1
unnamed: D14.C, R29.2
unnamed: D13.C, R32.2
unnamed: C37.2, U14.1, Y3.P$2
unnamed: C38.2, U14.2, Y3.P$1
unnamed: R34.2, R35.1, U15.1
unnamed: D16.A, F3.1, JP3.1
unnamed: D17.A, R35.2, U15.2, U15.4
unnamed: D18.A, R40.1
unnamed: D21.A, R44.1
unnamed: D20.C, R43.2
unnamed: D19.C, R46.2
unnamed: C52.2, U20.1, Y4.P$2
unnamed: C53.2, U20.2, Y4.P$1
unnamed: R48.2, R49.1, U21.1
unnamed: D22.A, F4.1, JP4.1
unnamed: D23.A, R49.2, U21.2, U21.4
unnamed: D24.A, R54.1
unnamed: D6.A, R8.1
RAW: J6.1, J8.1, S2.2, U3.3
RAW1: J17.1, J18.1, S3.2, U9.3
RAW2: J30.1, J31.1, S5.2, U15.3
RAW3: J43.1, J44.1, S7.2, U21.3
RXI: J6.10, U1.16
RXI1: J18.10, U8.16
RXI2: J31.10, U14.16
RXI3: J44.10, U20.16
RX_LED: R2.1, U1.48
RX_LED1: R15.1, U8.48
RX_LED2: R29.1, U14.48
RX_LED3: R43.1, U20.48
SCK: J7.4, U1.20, U6.1
SCK1: J21.4, U8.20, U11.1
SCK2: J34.4, U14.20, U17.1
SCK3: J47.4, U20.20, U23.1
SCK5V: U5.P$12, U6.20
SCK5V1: U10.P$12, U11.20
SCK5V2: U16.P$12, U17.20
SCK5V3: U22.P$12, U23.20
SCL: J11.4, J13.4, R14.1, U1.32
SCL1: J23.4, J24.4, R28.1, U8.32
SCL2: J36.4, J37.4, R42.1, U14.32
SCL3: J49.4, J50.4, R56.1, U20.32
SDA: J11.3, J13.3, R13.1, U1.31
SDA1: J23.3, J24.3, R27.1, U8.31
SDA2: J36.3, J37.3, R41.1, U14.31
SDA3: J49.3, J50.3, R55.1, U20.31
SHLD: J1.SHIELD, J1.SHIELD2, J1.SHIELD3, J1.SHIELD4, J1.SHIELD5, J1.SHIELD6, J1.SHIELD7, J1.SHIELD8, J1.SHIELD9, J1.SHIELD10
SHLD1: J2.SHIELD, J2.SHIELD2, J2.SHIELD3, J2.SHIELD4, J2.SHIELD5, J2.SHIELD6, J2.SHIELD7, J2.SHIELD8, J2.SHIELD9, J2.SHIELD10
SHLD2: J27.SHIELD, J27.SHIELD2, J27.SHIELD3, J27.SHIELD4, J27.SHIELD5, J27.SHIELD6, J27.SHIELD7, J27.SHIELD8, J27.SHIELD9, J27.SHIELD10
SHLD3: J40.SHIELD, J40.SHIELD2, J40.SHIELD3, J40.SHIELD4, J40.SHIELD5, J40.SHIELD6, J40.SHIELD7, J40.SHIELD8, J40.SHIELD9, J40.SHIELD10
SWDCLK: J14.4, U1.45
SWDCLK1: J26.4, U8.45
SWDCLK2: J39.4, U14.45
SWDCLK3: J52.4, U20.45
SWDIO: J14.2, U1.46
SWDIO1: J26.2, U8.46
SWDIO2: J39.2, U14.46
SWDIO3: J52.2, U20.46
TXO: J6.9, U1.15
TXO1: J18.9, U8.15
TXO2: J31.9, U14.15
TXO3: J44.9, U20.15
TX_LED: R3.1, U1.39
TX_LED1: R18.1, U8.39
TX_LED2: R32.1, U14.39
TX_LED3: R46.1, U20.39
USB_VCC: C3.2, C8.1, F1.2, J1.VBUS, J4.2, JP1.2
USB_VCC1: C17.2, C21.1, F2.2, J2.VBUS, J16.2, JP2.2
USB_VCC2: C32.2, C36.1, F3.2, J27.VBUS, J29.2, JP3.2
USB_VCC3: C47.2, C51.1, F4.2, J40.VBUS, J42.2, JP4.2
VBATT: C9.+, J3.2, J5.VIN0, J8.2, S2.3
VBATT1: C16.+, J15.2, J17.2, J25.VIN0, S3.3
VBATT2: C31.+, J28.2, J30.2, J38.VIN0, S5.3
VBATT3: C46.+, J41.2, J43.2, J51.VIN0, S7.3
VDDANA: C7.2, L1.2, U1.6
VDDANA1: C26.2, L2.2, U8.6
VDDANA2: C41.2, L3.2, U14.6
VDDANA3: C56.2, L4.2, U20.6

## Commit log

2018-07-19 Moved to hardware
2018-07-20 Intermediate save
2018-07-20 Intermediate
2018-07-20 Routed all wires
2018-07-20 Almost done
    ToDo: Ask for guidance on antenna traces, double check on if the same chip is used (to know how to connect DIO pins), get board/schem review, order
2018-07-20 Logging off
2018-07-23 Updates from board review
2018-07-24 Increased power trace width
2018-07-25 Updated power supply in schematic
2018-07-26 Started a re-route
2018-07-30 Progress capture
2018-07-30 Finalized hardware
2018-07-31 Finlized
2018-07-31 Finalizing
2018-08-16 Stuff
2018-08-22 Small changes
2018-08-31 Don't remember
2018-09-20 Finalizing things
2018-09-21 Organize, add test data and parser
2018-09-21 Add README.md
2018-09-26 x02 ready for review
2018-09-26 x02 ready for order
2018-10-02 Backup files
2018-10-03 Brought libraries into spec
2018-10-17 Update Hardware/SAMD21_Pro_RF_1W.b##
2018-10-24 Fixes
2018-10-25 Fixed silkscreen of "SPI" on top side
2018-11-14 Add partial support for Circuit/MicroPython

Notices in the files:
parts and their libraries:
SparkFun-Capacitors: Licensing: CC v3.0 Share-Alike You are welcome to use this library for commercial purposes.
SparkFun-LED: Licensing: Creative Commons ShareAlike 4.0 International - https://creativecommons.org/licenses/by-sa/4.0
SparkFun-Aesthetics: Released under the Creative Commons
